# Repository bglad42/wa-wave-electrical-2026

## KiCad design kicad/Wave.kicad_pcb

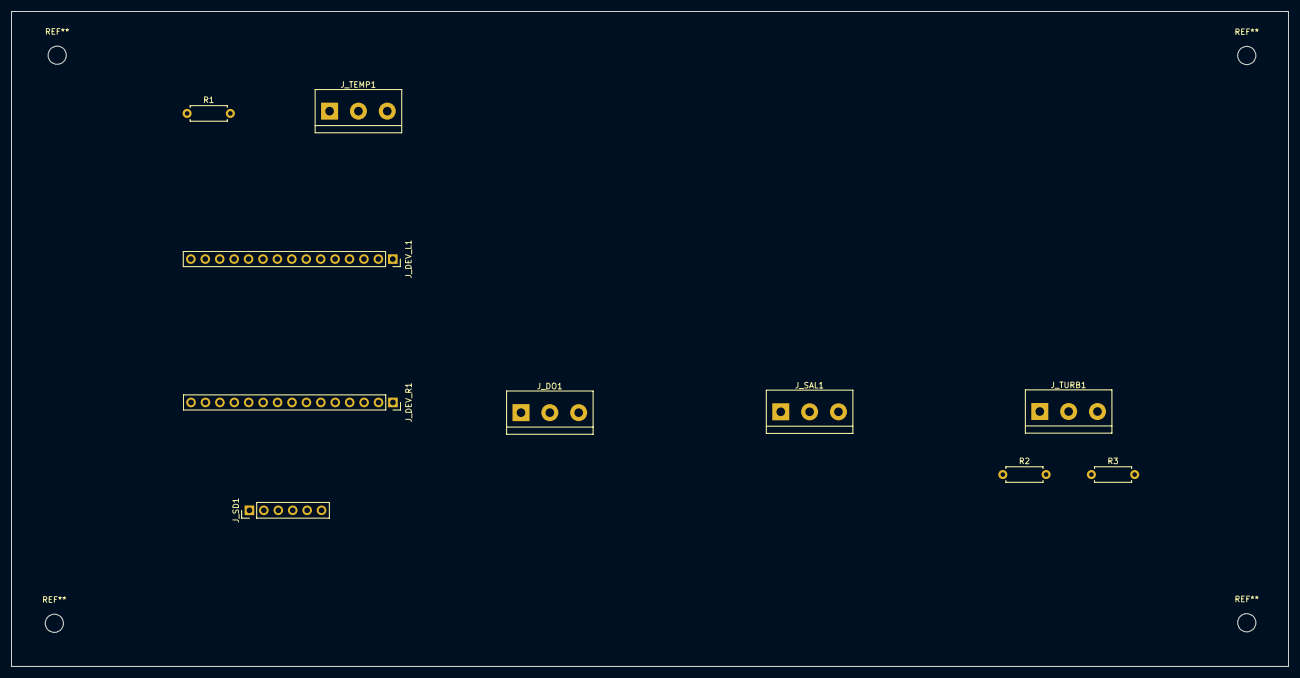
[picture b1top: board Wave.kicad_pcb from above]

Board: 2 copper layers, 224.9 x 115.4 mm, 10 parts (0 on the bottom side), 13 nets, no tracks yet.

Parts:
J_DEV_L1: Conn_01x15; PinSocket_1x15_P2.54mm_Vertical
J_DEV_R1: Conn_01x15; PinSocket_1x15_P2.54mm_Vertical
J_DO1: Conn_01x03; TerminalBlock_bornier-3_P5.08mm
J_SAL1: Conn_01x03; TerminalBlock_bornier-3_P5.08mm
J_SD1: Conn_01x06; PinHeader_1x06_P2.54mm_Vertical
J_TEMP1: Conn_01x03; TerminalBlock_bornier-3_P5.08mm
J_TURB1: Conn_01x03; TerminalBlock_bornier-3_P5.08mm
R1, R2: 4.7k; R_Axial_DIN0207_L6.3mm_D2.5mm_P7.62mm_Horizontal
R3: 10k; R_Axial_DIN0207_L6.3mm_D2.5mm_P7.62mm_Horizontal

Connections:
unnamed: J_DEV_L1.15 (5V), J_TURB1.1 (5V)
unnamed: J_DEV_L1.14 (GND), J_SAL1.3 (GND), J_TURB1.3 (GND), R3.2
unnamed: J_DEV_L1.7, J_DO1.2
unnamed: J_DEV_L1.6 (_SAL_AO), J_SAL1.2 (SAL_AO)
unnamed: J_DEV_R1.15 (3V3), J_DO1.1, J_SAL1.1 (3V3), J_SD1.1, J_TEMP1.1 (3V3), R1.1
unnamed: J_DEV_R1.14 (GND), J_DO1.3, J_SD1.2, J_TEMP1.3 (GND)
unnamed: J_DEV_R1.1, J_SD1.5
unnamed: J_DEV_R1.6, J_SD1.4
unnamed: J_DEV_R1.7, J_SD1.3
unnamed: J_DEV_R1.8, J_SD1.6
unnamed: J_DEV_R1.11 (_TEMP_DATA), J_TEMP1.2 (_TEMP_DATA), R1.2
unnamed: J_TURB1.2 (TURB_AO), R2.1
TURB_ADC: J_DEV_L1.4 (TURB_AO), R2.2, R3.1
